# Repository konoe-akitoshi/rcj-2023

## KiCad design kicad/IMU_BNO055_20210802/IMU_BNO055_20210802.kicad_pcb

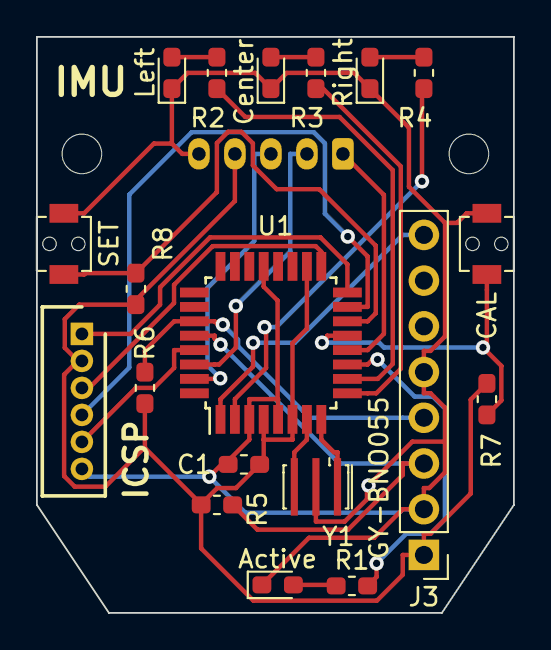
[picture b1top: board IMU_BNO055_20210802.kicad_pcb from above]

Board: 2 copper layers, 26.5 x 32.0 mm, 22 parts (1 on the bottom side), 24 nets.

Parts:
C1: 0.1u; C_0603_1608Metric_Pad1.05x0.95mm_HandSolder
D2: Active; LED_0603_1608Metric_Pad1.05x0.95mm_HandSolder
D3: Left; LED_0603_1608Metric_Pad1.05x0.95mm_HandSolder
D4: Center; LED_0603_1608Metric_Pad1.05x0.95mm_HandSolder
D5: Right; LED_0603_1608Metric_Pad1.05x0.95mm_HandSolder
J1: ICSP; JSTB6B-ZR
J2: SerialOUT; JST_PH_S5B-PH-K_1x05_P2.00mm_Horizontal
J3: GY-BNO055; PinHeader_1x08_P2.54mm_Vertical
R1, R2, R3, R4: 120; R_0603_1608Metric_Pad1.05x0.95mm_HandSolder
R5, R6, R7, R8: 10k; R_0603_1608Metric_Pad1.05x0.95mm_HandSolder
REF01, REF02: MountingHole_2.2mm_M2
SW1: CAL; TVAF06-A020B-R
SW2: SET; TVAF06-A020B-R
U1: ATmega328P-AU; TQFP-32_7x7mm_P0.8mm
Y1: X`Tal 16MHz; Resonator_SMD_muRata_CSTxExxV-3Pin_3.0x1.1mm_HandSoldering

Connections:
+5V: C1.1, J1.2, J2.4, J3.1, R5.1, R6.1, R7.1, R8.1, U1.4, U1.6, U1.18
GND: C1.2, D2.1, D3.1, D4.1, D5.1, J1.6, J2.5, J3.2, J3.5, SW1.2, SW2.2, U1.3, U1.5, U1.21, Y1.2
unnamed: D2.2, R1.1
unnamed: D3.2, R2.1
unnamed: D4.2, R3.1
unnamed: D5.2, R4.1
unnamed: J1.1, U1.16
unnamed: J1.3, U1.17
unnamed: J1.4, U1.15
unnamed: J1.5, U1.29
unnamed: J2.1, U1.12
unnamed: J2.2, U1.30
unnamed: J2.3, U1.31
unnamed: J3.3, R5.2, U1.28
unnamed: J3.4, R6.2, U1.27
unnamed: J3.8, U1.1
unnamed: R1.2, U1.11
unnamed: R2.2, U1.10
unnamed: R3.2, U1.9
unnamed: R4.2, U1.2
unnamed: R7.2, SW1.1, U1.13
unnamed: R8.2, SW2.1, U1.14
unnamed: U1.7, Y1.3
unnamed: U1.8, Y1.1

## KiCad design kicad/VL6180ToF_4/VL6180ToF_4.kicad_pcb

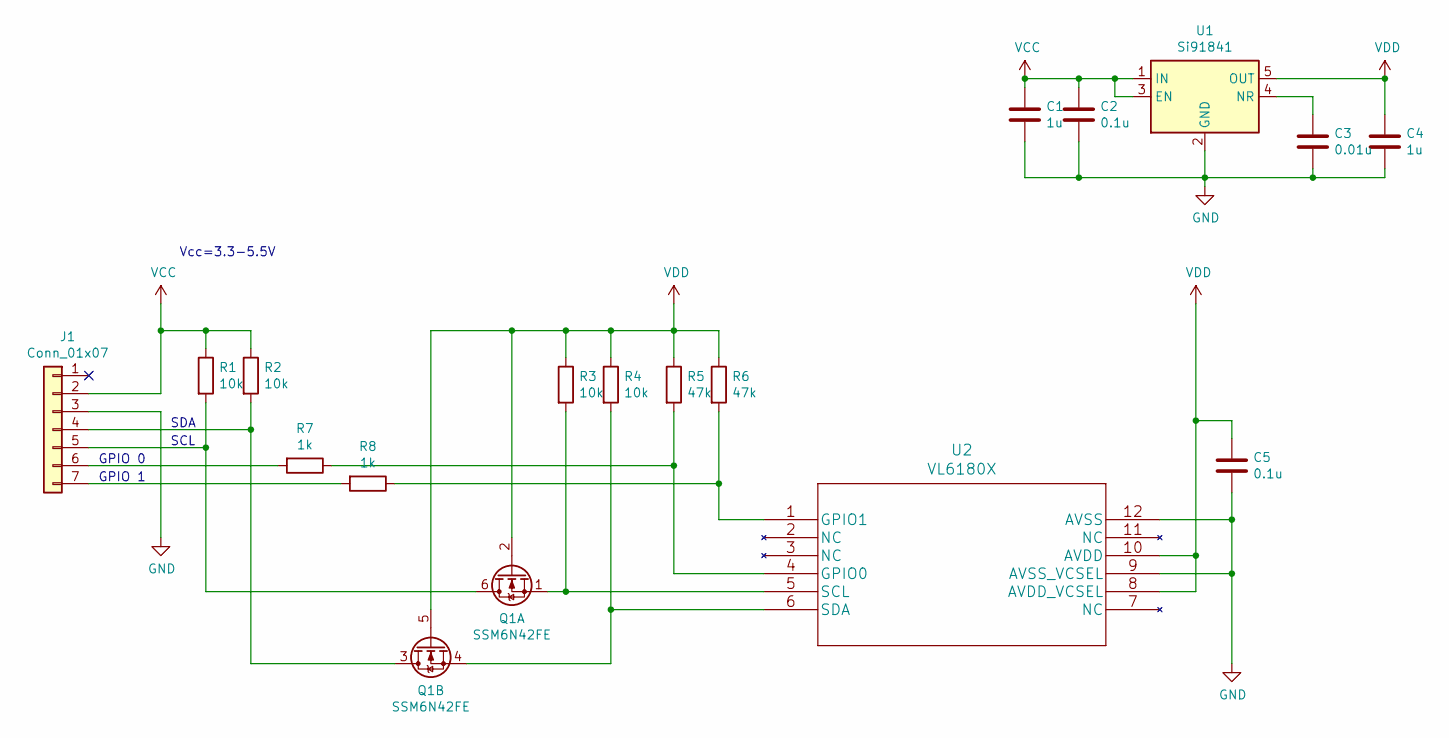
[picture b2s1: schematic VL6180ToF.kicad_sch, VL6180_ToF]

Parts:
C1, C4: 1u; C_0603_1608Metric
C2, C5: 0.1u; C_0603_1608Metric
C3: 0.01u; C_0603_1608Metric
J1: Conn_01x07; Pin_1x07_P1.27mm_SMD
Q1: SSM6N42FE; WSON-6_1.5x1.5mm_P0.5mm
R1, R2, R3, R4: 10k; R_0603_1608Metric
R5, R6: 47k; R_0603_1608Metric
R7, R8: 1k; R_0603_1608Metric
U1: Si91841; SOT-23-5
U2: VL6180X; VL6180XV0NR&slash_1

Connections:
GND: C1.2, C2.2, C3.2, C4.2, C5.2, J1.3, U1.2 (GND), U2.9 (AVSS_VCSEL), U2.12 (AVSS)
unnamed: C3.1, U1.4 (NR)
unnamed: J1.4, Q1.3 (D), R2.2
unnamed: J1.5, Q1.6 (D), R1.2
unnamed: J1.6, R7.2
unnamed: J1.7, R8.2
unnamed: Q1.1 (S), R3.2, U2.5 (SCL)
unnamed: Q1.4 (S), R4.2, U2.6 (SDA)
unnamed: R5.2, R7.1, U2.4 (GPIO0)
unnamed: R6.2, R8.1, U2.1 (GPIO1)
VCC: C1.1, C2.1, J1.2, R1.1, R2.1, U1.1 (IN), U1.3 (EN)
VDD: C4.1, C5.1, Q1.2 (G), Q1.5 (G), R3.1, R4.1, R5.1, R6.1, U1.5 (OUT), U2.8 (AVDD_VCSEL), U2.10 (AVDD)

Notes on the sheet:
GPIO 0
SDA
SCL
GPIO 1
Vcc=3.3-5.5V

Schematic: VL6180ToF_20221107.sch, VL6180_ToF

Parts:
C1, C4: 1u; C_0603_1608Metric
C2, C5: 0.1u; C_0603_1608Metric
C3: 0.01u; C_0603_1608Metric
J1: Conn_01x07; PinHeader_1x07_P1.27mm_Vertical
Q1: SSM6N42FE; WSON-6_1.5x1.5mm_P0.5mm
R1, R2, R3, R4: 10k; R_0603_1608Metric
R5, R6: 47k; R_0603_1608Metric
R7, R8: 1k; R_0603_1608Metric
U1: Si91841; SOT-23-5
U2: VL6180X; VL6180XV0NR&slash_1

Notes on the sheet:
SDA
SCL
GPIO 0
GPIO 1
Vcc=3.3-5.5V

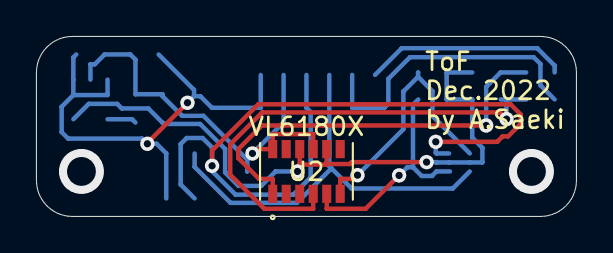
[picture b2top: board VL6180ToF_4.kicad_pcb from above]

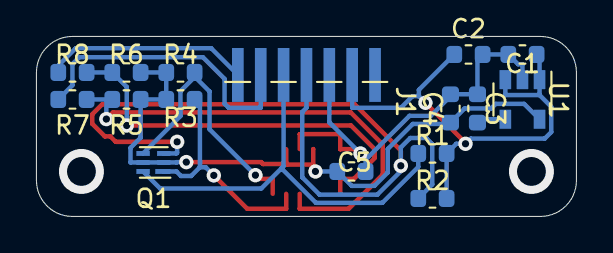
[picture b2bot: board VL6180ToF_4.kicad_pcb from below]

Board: 2 copper layers, 30.0 x 10.0 mm, 17 parts (16 on the bottom side), 12 nets.

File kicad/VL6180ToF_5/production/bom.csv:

Designator,Footprint,Quantity,Value,LCSC Part #
C1,0603,1,1u,
C2,0603,1,0.1u,
C3,0603,1,0.01u,
C4,0603,1,1u,
C5,0603,1,0.1u,
J1,Pin_1x07_P1.27mm_SMD,1,Conn_01x07,
Q1,WSON-6_1.5x1.5mm_P0.5mm,1,SSM6N42FE,
R1,0603,1,10k,
R2,0603,1,10k,
R3,0603,1,10k,
R4,0603,1,10k,
R5,0603,1,47k,
R6,0603,1,47k,
R7,0603,1,1k,
R8,0603,1,1k,
U1,SOT-23-5,1,Si91841,
U2,VL6180XV0NR&slash_1,1,VL6180X,

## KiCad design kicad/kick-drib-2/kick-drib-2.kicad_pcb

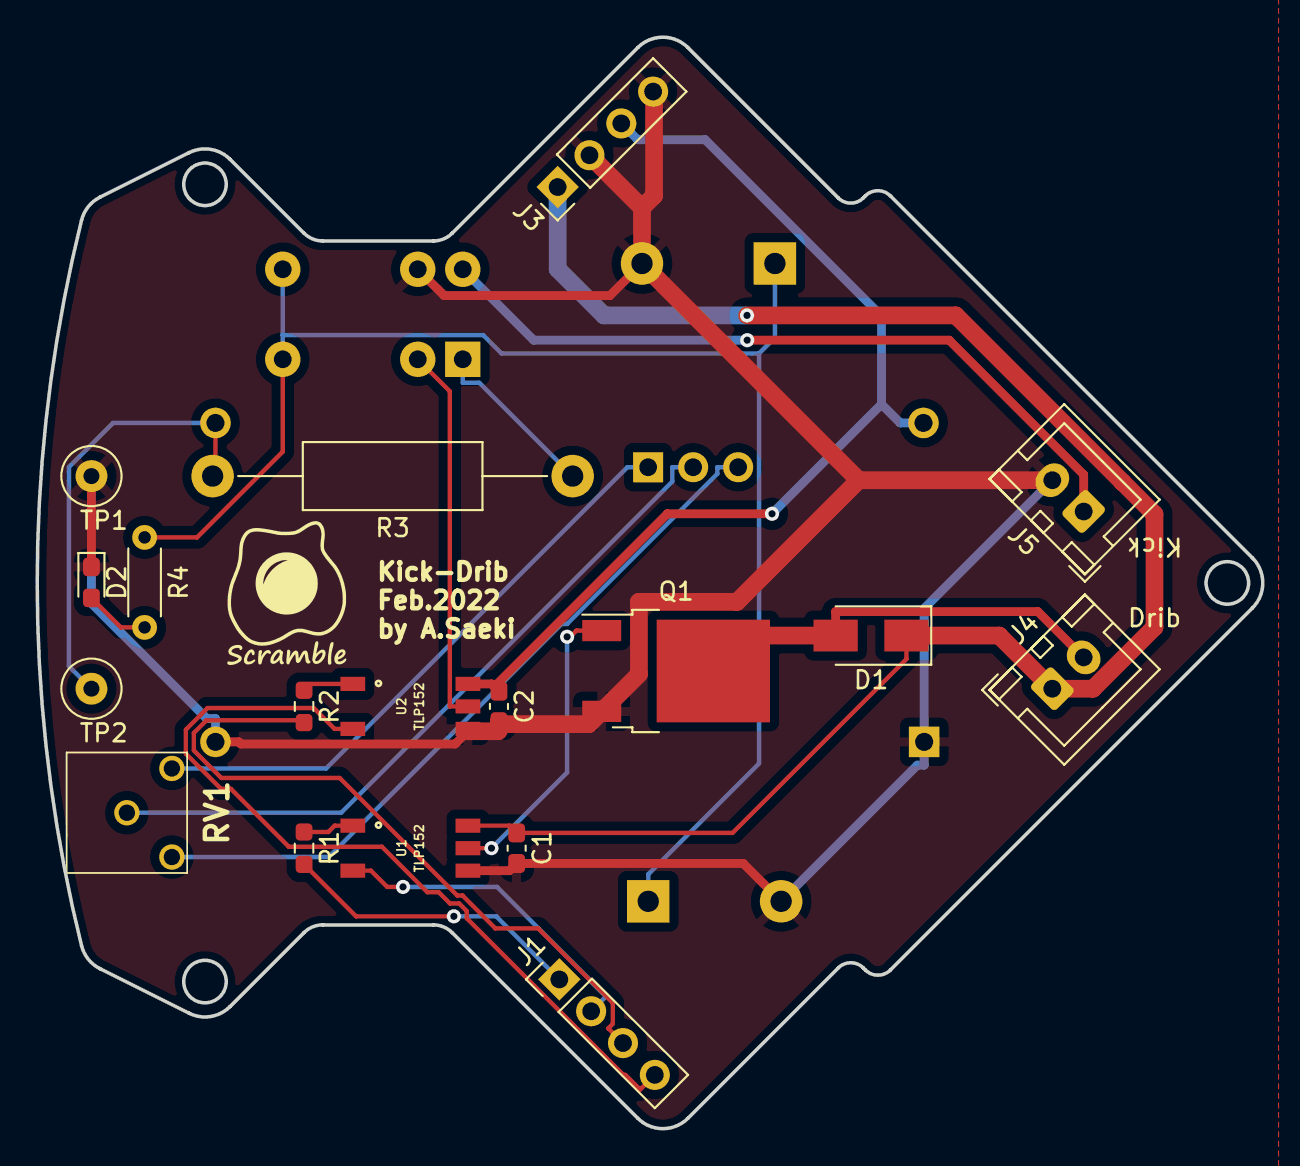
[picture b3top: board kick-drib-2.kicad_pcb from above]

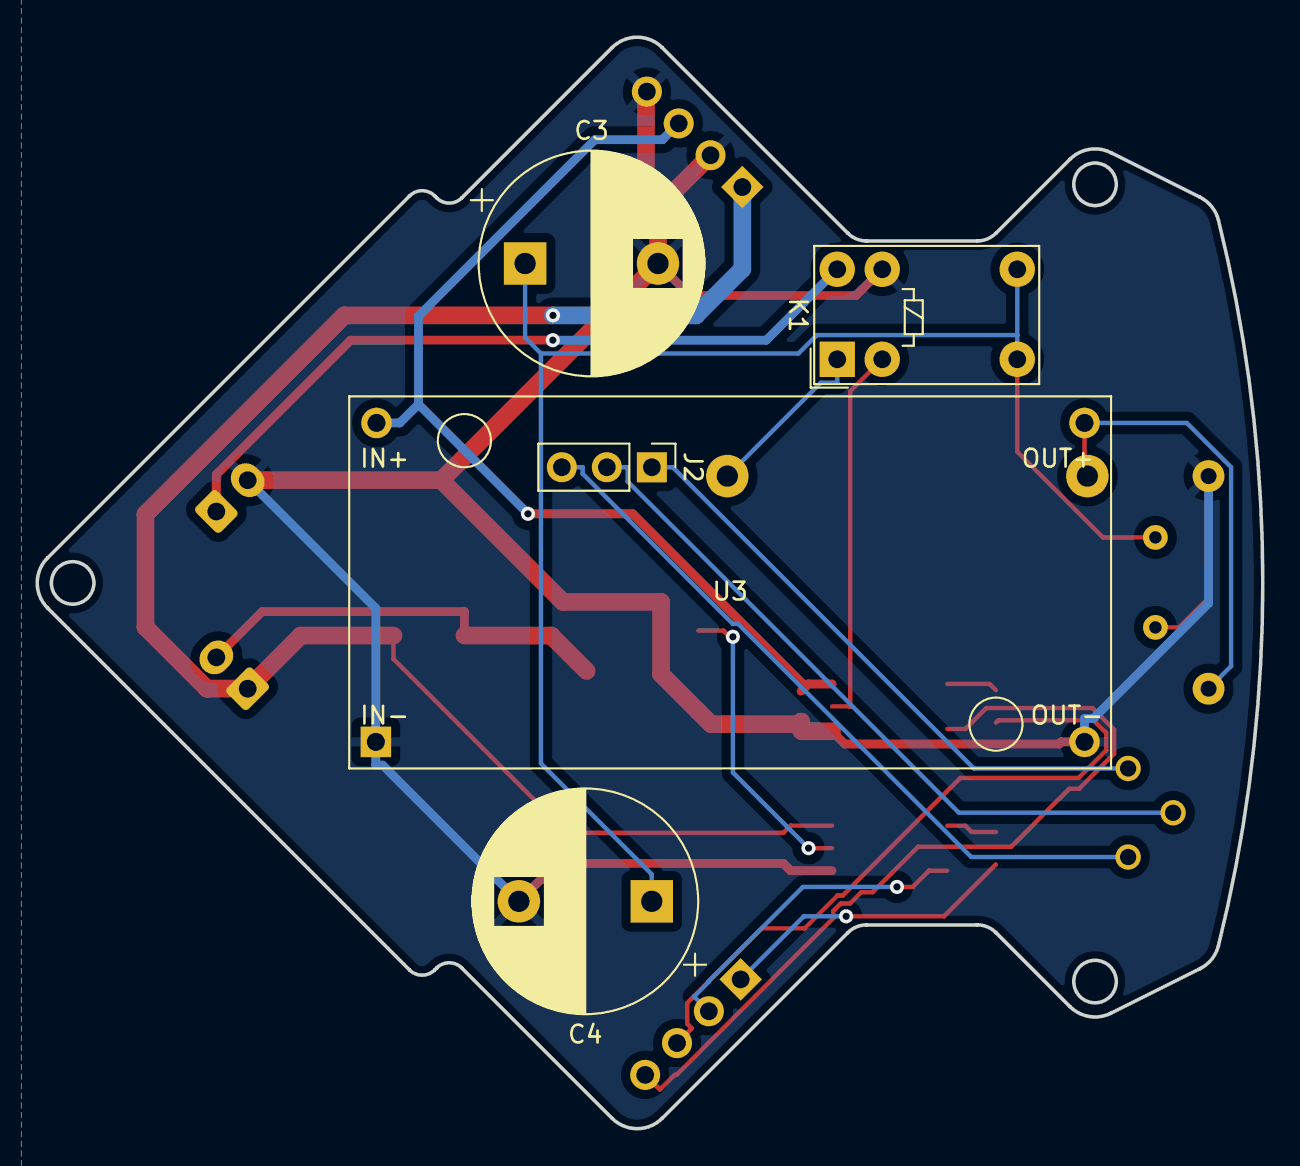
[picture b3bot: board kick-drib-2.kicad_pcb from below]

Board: 2 copper layers, 69.2 x 61.6 mm, 23 parts (5 on the bottom side), 20 nets.

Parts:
C1, C2: 1uF; C_0603_1608Metric_Pad1.08x0.95mm_HandSolder
C3, C4: 1000uF/50V; CP_Radial_D12.5mm_P7.50mm
D1: SX34F; D_SMA
D2: LED; LED_0603_1608Metric_Pad1.05x0.95mm_HandSolder
J1: drib-kick; PinHeader_1x04_P2.54mm_Vertical
J2: Conn_01x03; PinHeader_1x03_P2.54mm_Vertical
J3: drib-kick_POWER; PinHeader_1x04_P2.54mm_Vertical
J4: DribblerMotor; JST_XH_B2B-XH-A_1x02_P2.50mm_Vertical
J5: Kicker1; JST_XH_B2B-XH-A_1x02_P2.50mm_Vertical
K1: G5V-1/12V; Relay_SPDT_Omron_G5V-1
Q1: NP52N06SLG; TO-252-2
R1, R2: 120; R_0603_1608Metric_Pad0.98x0.95mm_HandSolder
R3: 100; R_Axial_DIN0411_L9.9mm_D3.6mm_P20.32mm_Horizontal
R4: 30k; R_Axial_DIN0204_L3.6mm_D1.6mm_P5.08mm_Horizontal
RV1: 20k; Trim-GF063X
TP1: GND; TestPoint_Loop_D2.60mm_Drill0.9mm_Beaded
TP2: V+; TestPoint_Loop_D2.60mm_Drill0.9mm_Beaded
U1, U2: TLP152
U3: XL6009/HW-432; XL6009_HW432

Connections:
+15V: C2.1, J3.3, U2.6 (VCC), U3.2 (+VIN)
GND: C1.2, C2.2, C3.2, C4.2, D2.1 (K), J3.2, J3.4, J5.2, K1.9, Q1.3 (S), TP1.1, U1.4 (GND), U2.4 (GND), U3.1 (-VIN), U3.3 (-VOUT)
unnamed: C1.1, D1.1 (K), J3.1, J4.1, U1.6 (VCC)
unnamed: C3.1, C4.1, K1.5, K1.6, R4.1
unnamed: D1.2 (A), J4.2, Q1.2 (D)
unnamed: D2.2 (A), R4.2
unnamed: J1.1, R1.2
unnamed: J1.2, U1.3
unnamed: J1.3, R2.2
unnamed: J1.4, U2.3
unnamed: J2.1, RV1.1
unnamed: J2.2, RV1.2
unnamed: J2.3, RV1.3
unnamed: J5.1, K1.10
unnamed: K1.1, R3.1
unnamed: K1.2, U2.5 (VO)
unnamed: Q1.1 (G), U1.5 (VO)
unnamed: R1.1, U1.1
unnamed: R2.1, U2.1
unnamed: R3.2, TP2.1, U3.4 (+VOUT)

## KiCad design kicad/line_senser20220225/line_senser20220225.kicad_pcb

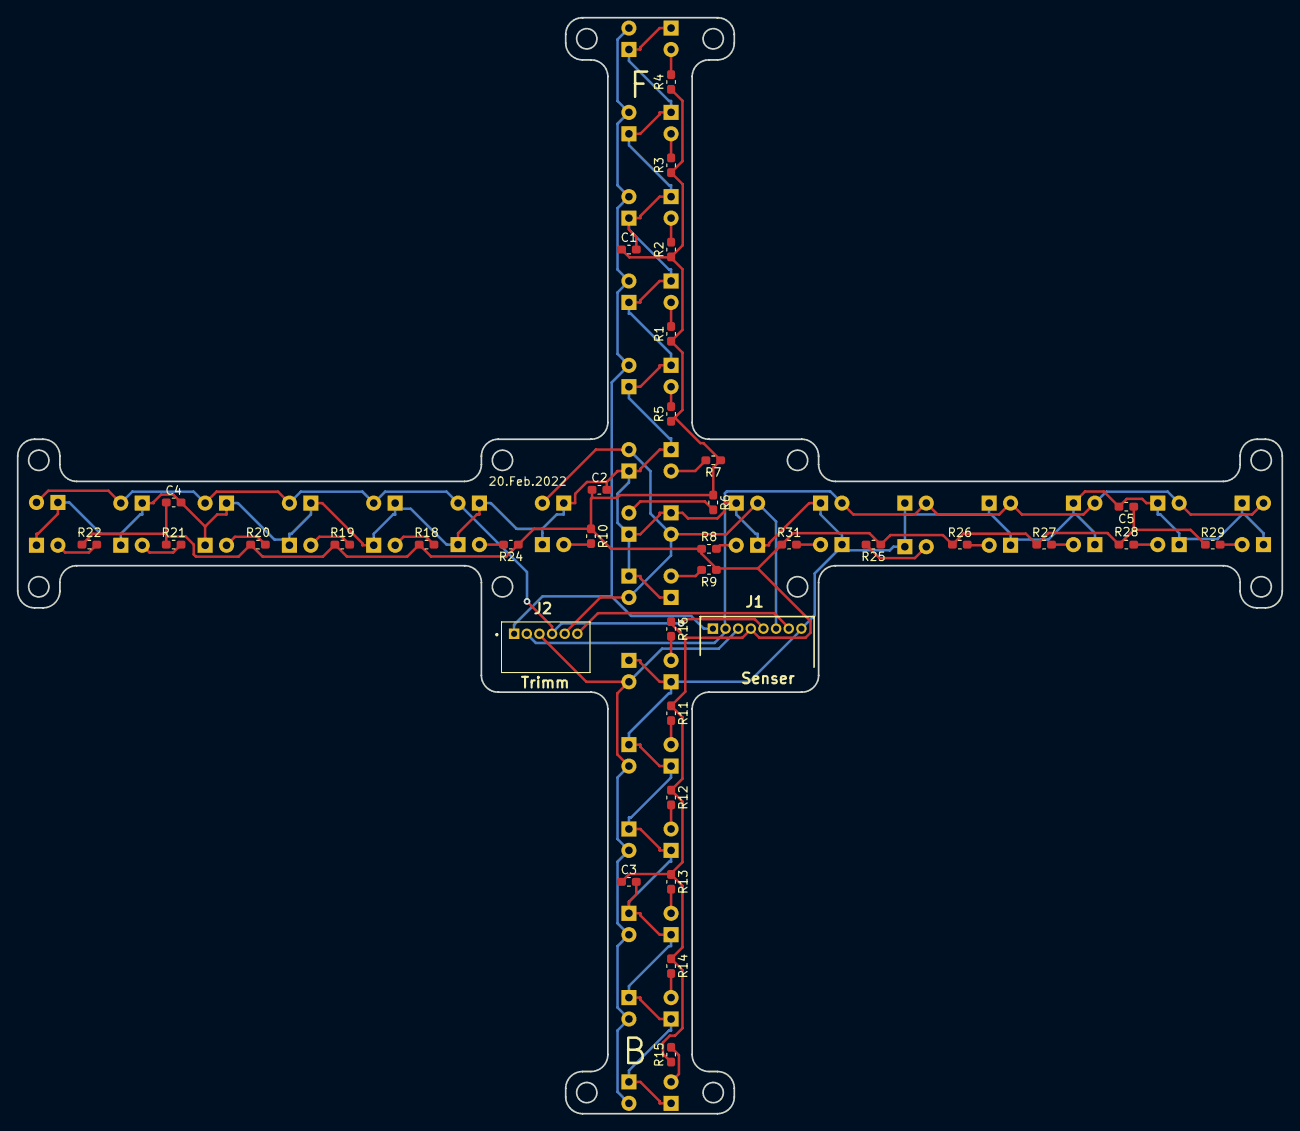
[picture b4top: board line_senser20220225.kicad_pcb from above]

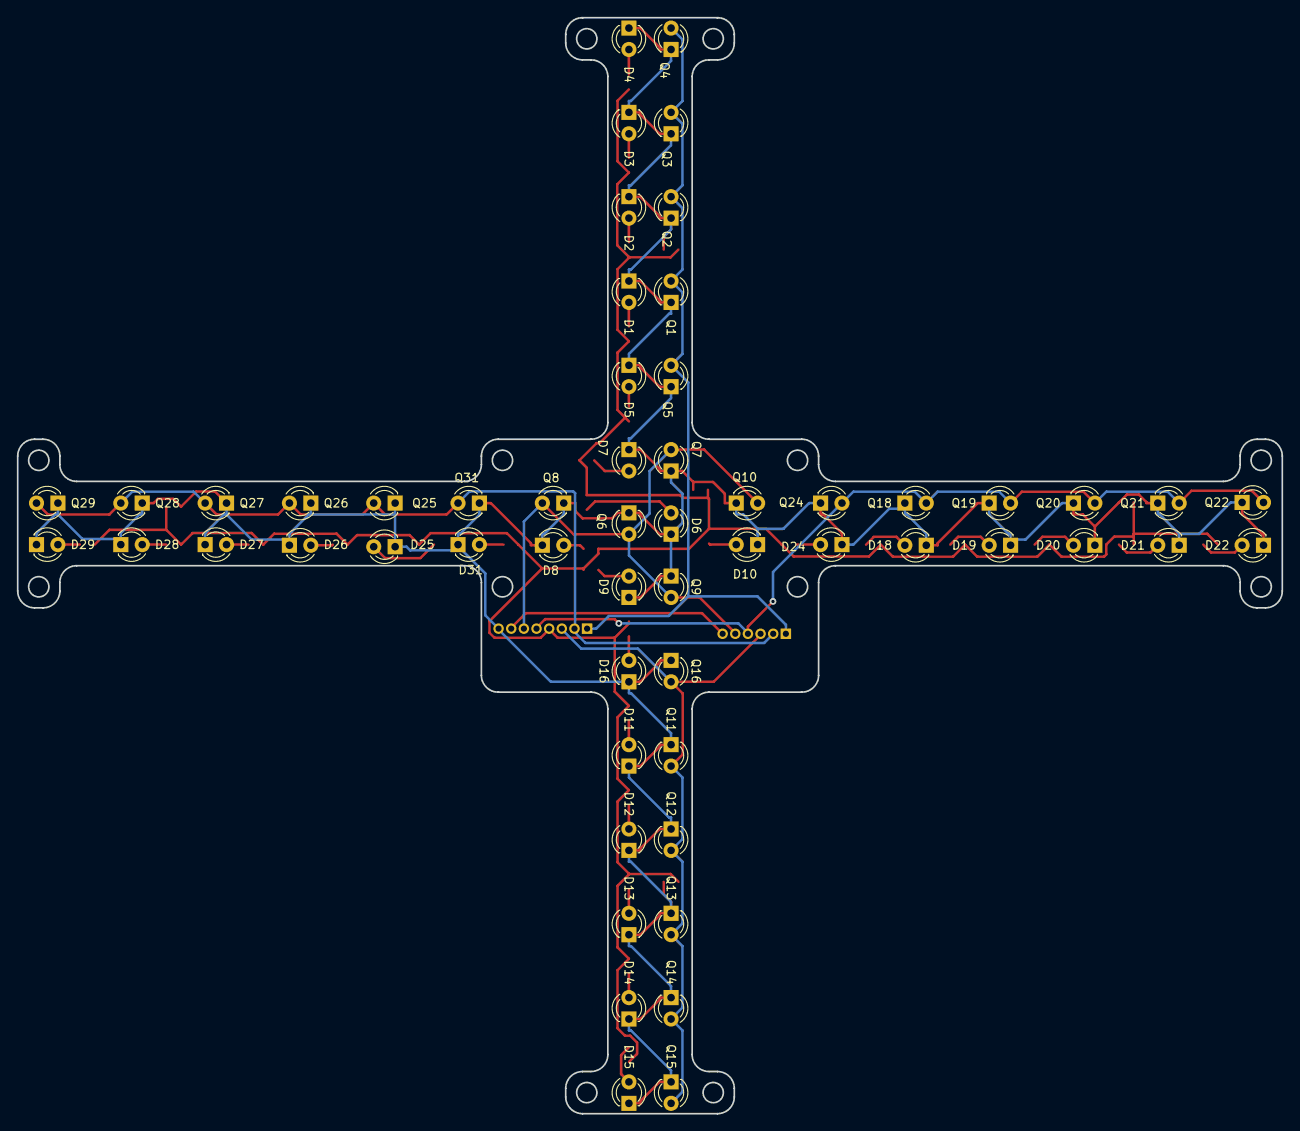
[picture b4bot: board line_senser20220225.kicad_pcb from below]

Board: 2 copper layers, 150.0 x 130.0 mm, 91 parts (56 on the bottom side), 36 nets.

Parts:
C1, C2, C3, C4, C5: 10u; C_0603_1608Metric_Pad1.05x0.95mm_HandSolder
D1, D2, D3, D4, D5, D6, D7, D8, D9, D10, D11, D12, D13, D14, D15, D16, D18, D19, D20, D21, D22, D24, D25, D26, D27, D28, D29, D31: LED; OSW54K3131A
J1: Senser; JSTS8B-ZRLFSN
J2: Trimm; JSTS6B-ZRLFSN
Q1, Q2, Q3, Q4, Q5, Q6, Q7, Q8, Q9, Q10, Q11, Q12, Q13, Q14, Q15, Q16, Q18, Q19, Q20, Q21, Q22, Q24, Q25, Q26, Q27, Q28, Q29, Q31: Q_Photo; NJL7502L
R1, R2, R3, R4, R5, R6, R7, R8, R9, R10, R11, R12, R13, R14, R15, R16, R18, R19, R20, R21, R22, R24, R25, R26, R27, R28, R29, R31: 470; R_0603_1608Metric_Pad1.05x0.95mm_HandSolder

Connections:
unnamed: C1.1, C2.1, C3.1, C4.1, C5.1, J1.4, R1.1, R2.1, R3.1, R4.1, R5.1, R6.1, R7.1, R8.1, R9.1, R10.1, R11.1, R12.1, R13.1, R14.1, R15.1, R16.1, R18.1, R19.1, R20.1, R21.1, R22.1, R24.1, R25.1, R26.1, R27.1, R28.1, R29.1, R31.1
unnamed: C1.2, C2.2, C3.2, C4.2, C5.2, D1.1 (K), D2.1 (K), D3.1 (K), D4.1 (K), D5.1 (K), D6.1 (K), D7.1 (K), D8.1 (K), D9.1 (K), D10.1 (K), D11.1 (K), D12.1 (K), D13.1 (K), D14.1 (K), D15.1 (K), D16.1 (K), D18.1 (K), D19.1 (K), D20.1 (K), D21.1 (K), D22.1 (K), D24.1 (K), D25.1 (K), D26.1 (K), D27.1 (K), D28.1 (K), D29.1 (K), D31.1 (K), J1.8, Q1.1 (E), Q2.1 (E), Q3.1 (E), Q4.1 (E), Q5.1 (E), Q6.1 (E), Q7.1 (E), Q8.1 (E), Q9.1 (E), Q10.1 (E), Q11.1 (E), Q12.1 (E), Q13.1 (E), Q14.1 (E), Q15.1 (E), Q16.1 (E), Q18.1 (E), Q19.1 (E), Q20.1 (E), Q21.1 (E), Q22.1 (E), Q24.1 (E), Q25.1 (E), Q26.1 (E), Q27.1 (E), Q28.1 (E), Q29.1 (E), Q31.1 (E)
unnamed: D1.2 (A), R1.2
unnamed: D2.2 (A), R2.2
unnamed: D3.2 (A), R3.2
unnamed: D4.2 (A), R4.2
unnamed: D5.2 (A), R5.2
unnamed: D6.2 (A), R6.2
unnamed: D7.2 (A), R7.2
unnamed: D8.2 (A), R8.2
unnamed: D9.2 (A), R9.2
unnamed: D10.2 (A), R10.2
unnamed: D11.2 (A), R11.2
unnamed: D12.2 (A), R12.2
unnamed: D13.2 (A), R13.2
unnamed: D14.2 (A), R14.2
unnamed: D15.2 (A), R15.2
unnamed: D16.2 (A), R16.2
unnamed: D18.2 (A), R18.2
unnamed: D19.2 (A), R19.2
unnamed: D20.2 (A), R20.2
unnamed: D21.2 (A), R21.2
unnamed: D22.2 (A), R22.2
unnamed: D24.2 (A), R24.2
unnamed: D25.2 (A), R25.2
unnamed: D26.2 (A), R26.2
unnamed: D27.2 (A), R27.2
unnamed: D28.2 (A), R28.2
unnamed: D29.2 (A), R29.2
unnamed: D31.2 (A), R31.2
unnamed: J1.1, J2.1, Q1.2 (C), Q2.2 (C), Q3.2 (C), Q4.2 (C), Q5.2 (C)
unnamed: J1.2, J2.2, Q25.2 (C), Q26.2 (C), Q27.2 (C), Q28.2 (C), Q29.2 (C), Q31.2 (C)
unnamed: J1.3, J2.3, Q11.2 (C), Q12.2 (C), Q13.2 (C), Q14.2 (C), Q15.2 (C), Q16.2 (C)
unnamed: J1.5, J2.4, Q18.2 (C), Q19.2 (C), Q20.2 (C), Q21.2 (C), Q22.2 (C), Q24.2 (C)
unnamed: J1.6, J2.5, Q6.2 (C), Q7.2 (C), Q8.2 (C), Q9.2 (C), Q10.2 (C)
unnamed: J1.7, J2.6

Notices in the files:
parts and their libraries:
Copyright 2021 Accelerated Designs. All rights reserved.
